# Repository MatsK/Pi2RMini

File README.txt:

Pi2RMini 
2013-2014 Logan Microelectronics

Small power switch for the Raspberry Pi. Free to use, modify, and distribute with proper attribution. This directory holds the current schematic and layout (Eagle v6.1.0), single layer PDF (not mirrored), code for ATTiny13 and Raspberry Pi, and older versions.

awjlogan@gmail.com
awjlogan.wordpress.com

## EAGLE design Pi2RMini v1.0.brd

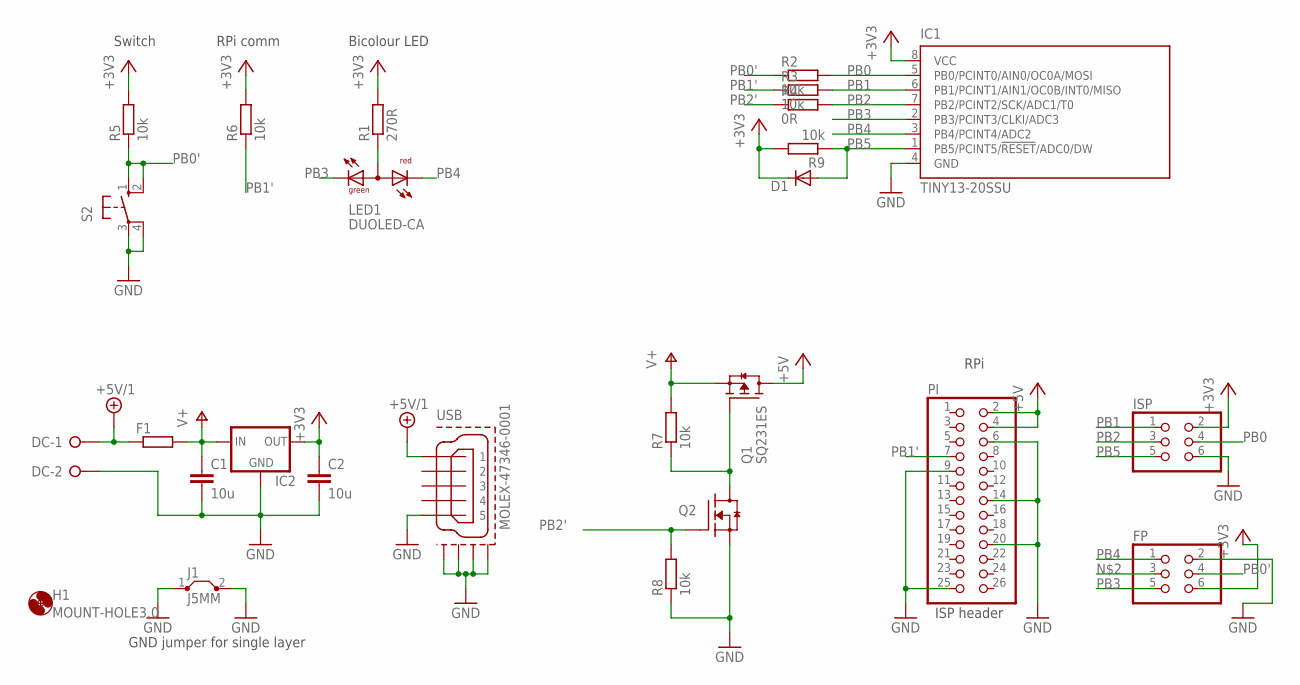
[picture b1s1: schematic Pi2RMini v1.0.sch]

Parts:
C1, C2: 10u; C0805
D1: DIODE-MICROMELF-R; MICROMELF-R
DC: W237-02P; W237-132
F1: R-EU_R1210; R1210
FP: PINHD-2X3; 2X03
H1: MOUNT-HOLE3.0; 3,0
IC1: TINY13-20SSU; 8S1
IC2: MCP1700TT; SOT-23
ISP: PINHD-2X3; 2X03
J1: J5MM; 05
LED1: DUOLED-CA; SOT-23
PI: PINHD-2X13; 2X13
Q1: SQ231ES; SOT-23
Q2: 2N7002; SOT-23
R1: 270R; R0805
R2, R3, R5, R6, R7, R8, R9: 10k; R0805
R4: 0R; R0805
S2: 10-XX; B3F-10XX
USB: MOLEX-47346-0001; MOLEX-47364-0001

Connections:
+3V3: C2.1, D1.C, FP.6, IC1.8 (VCC), IC2.2 (OUT), ISP.2, R1.2, R5.2, R6.2, R9.2
+5V: PI.2, PI.4, Q1.3 (D)
+5V/1: DC.1, F1.1, USB.1
GND: C1.2, C2.2, DC.2, FP.2, IC1.4 (GND), IC2.1 (GND), ISP.6, J1.1, J1.2, PI.6, PI.9, PI.14, PI.20, PI.25, Q2.2 (S), R8.1, S2.3, S2.4 (P1), USB.5, USB.GND1, USB.GND2, USB.GND3, USB.GND4
unnamed: FP.3, LED1.3 (A), R1.1
unnamed: Q1.1 (G), Q2.3 (D), R7.1
PB0: IC1.5 (PB0/PCINT0/AIN0/OC0A/MOSI), ISP.4, R2.2
PB0': FP.4, R2.1, R5.1, S2.1 (S), S2.2 (S1)
PB1: IC1.6 (PB1/PCINT1/AIN1/OC0B/INT0/MISO), ISP.1, R3.2
PB1': PI.7, R3.1, R6.1
PB2: IC1.7 (PB2/PCINT2/SCK/ADC1/T0), ISP.3, R4.2
PB2': Q2.1 (G), R4.1, R8.2
PB3: FP.5, IC1.2 (PB3/PCINT3/CLKI/ADC3), LED1.2 (CG)
PB4: FP.1, IC1.3 (PB4/PCINT4/ADC2), LED1.1 (CR)
PB5: D1.A, IC1.1 (PB5/PCINT5/!RESET!/ADC0/DW), ISP.5, R9.1
V+: C1.1, F1.2, IC2.3 (IN), Q1.2 (S), R7.2

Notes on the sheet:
Switch
RPi comm
Bicolour LED
GND jumper for single layer
ISP header
RPi

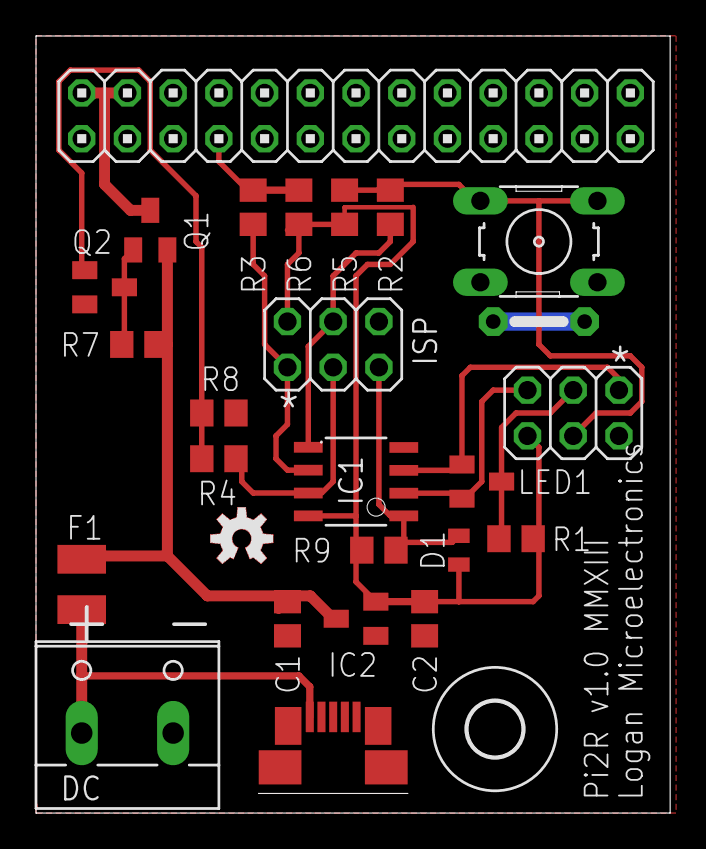
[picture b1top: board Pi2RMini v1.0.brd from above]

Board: 2 copper layers, 35.2 x 43.2 mm, 26 parts (0 on the bottom side), 16 nets.

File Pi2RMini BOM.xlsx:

Pi2RMini BOM file
Sch. # | Part | Package | Farnell Code | Price / 100 | Notes |  | Total ex. VAT | 2.2409999999999997
C1 | 10u ceramic | 0805 | 1288204 | 6.6000000000000003E-2 |  |  | VAT | 0.44819999999999993
C2 | 10u ceramic | 0805 | 1288204 | 6.6000000000000003E-2 |  |  | Total | 2.6891999999999996
IC1 | ATtiny13 | SOIC8 | 1715519 | 0.36
IC2 | MCP1700 | SOT23 | 1296952 | 0.19700000000000001 |  |  | Total parts
Q2 | 2N7002 | SOT23 | 2317616 | 0.02 |  |  | Total unique
Q1 | SQ2319ES | SOT23 | 1869886 | 0.32
USB | micro USB B | n/a | 1568026 | 0.48 | optional
LED1 | Bicolour LED | SOT23 | 2146479 | 0.17399999999999999 | optional
R1 | 270R | 0805 | 2331788 | 6.0000000000000001E-3
R2 | 10K | 0805 | 2331808 | 6.0000000000000001E-3
R3 | 10K | 0805 | 2331808 | 6.0000000000000001E-3
R4 | 0R | jumper
R5 | 10K | 0805 | 2331808 | 6.0000000000000001E-3
R6 | 10K | 0805 | 2331808 | 6.0000000000000001E-3
R7 | 10K | 0805 | 2331808 | 6.0000000000000001E-3
R8 | 10K | 0805 | 2331823 | 6.0000000000000001E-3
ISP | 2x3 header | n/a | 1248132 | 0.23
FP | 2x3 header | n/a | 1248132 | 0.23
SW | switch | n/a | 9471731 | 3.7999999999999999E-2
R9 | 10K | 0805 | 2331808 | 6.0000000000000001E-3
D1 | LL4148 | miniMELF | 7355513 | 1.2E-2 | optional

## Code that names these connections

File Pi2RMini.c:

/*
 * Pi2RMini.c
 *
 * Pi2R Mini device firmware for v1.0 boards
 * Logan Microelectronics 2013-2014
 * http://awjlogan.wordpress.com
 * https://github.com/awjlogan/pi2rmini
 *
 * Written in AVR Studio 5 for AVR GCC
 * Target: Atmel ATTiny13
 * 4.8 MHz internal osscilator / 8 = 600 kHz
 * Pins:	1	!RST					PB5
 *			2	Green LED				PB3
 *			3	Red LED					PB4
 *			4	GND		
 *			5	Switch					PB0
 *			6	RPi communication line	PB1
 *			7	RPi MOSET				PB2
 *			8	+3V3
 *
 * Fuse calculated:		69 FF (http://www.engbedded.com/fusecalc)
 * avrdude arguments:	-U lfuse:w:0x69:m -U hfuse:w:0xff:m
 * for: 4.8 MHz int osc, 14CK + 64 ms startup, CKDIV, no WDT, SPI enabled, !RST enabled, no BOD
 *
 * To change the startup, reset, and shutdown delays, alter lines with 'seconds = xx'. The TMR0 interrupt hits every
 * ~100 ms, so the seconds value should be 'delay in seconds x 10'. The variable 'flash' acts in the same way.
*/			

#define F_CPU		600000UL

#include <avr/io.h>
#include <avr/interrupt.h>
#include <util/delay.h>

// Status register definitions
#define	PI_ERROR	1
#define PI_ON		8
#define PI_OFF		16
#define BUTTON		32

#define PI_COMM		PINB1

// Pin assignments
#define SW			0x01
#define PI_FET		0x04
#define LED_G		0x08
#define LED_R		0x10

// common cathode status LED on/off
#define RED_OFF		PORTB &= ~(LED_R)
#define RED_ON		PORTB |= LED_R
#define GRN_OFF		PORTB &= ~(LED_G)
#define GRN_ON		PORTB |= LED_G

// Function prototypes
static void setup(void);
static void button(void);
static void reset(void);

// Global variables
static volatile uint8_t state = 0;
static volatile uint8_t flash = 0;
static volatile uint_least16_t seconds = 0;

int main(void)
{
	setup();
	state |= PI_OFF;
	RED_ON;
	GRN_OFF;
	
	// check status registers and respond
	while(1)
    {	
		if (state & BUTTON) {
			// disable PCINT while button press is handled
			PCMSK &= ~(1<<PCINT0);
			state &= ~(BUTTON);
			_delay_ms(50);					// debounce
			if (!(PINB & PINB0)) {
				button();
			}
			PCMSK |= (1<<PCINT0);
		}
		
		// flash red LED if in error state
		if (state & PI_ERROR) {
			if (!flash) {
				PORTB ^= LED_R;
				flash = 2;
			}
		}
	}	
}

static void button(void) {
	if (state & PI_OFF) {
		state = PI_ON;
		PORTB |= PI_FET;
		GRN_ON;
		RED_ON;
		
		// wait 60 secs for RPi to start up
		seconds = 600;
		while(PINB & (1<<PI_COMM)) {
			if (!seconds) {
				state |= PI_ERROR;
				GRN_OFF;
				return;
			}
		}
		RED_OFF;
		return;
	}
	
	if (state & PI_ON) {
		// check for forced reset - 4 s press
		seconds = 40;
		RED_ON;
		GRN_OFF;
		while (!(PINB & (1<<PINB0))) {
			// flash red/green
			if (!flash) {
				PORTB ^= (LED_G + LED_R);
				flash = 2;
			}
			// time up, reset!
			if (!seconds) {
				cli();
				reset();
				while(!(PINB & (1<<PINB0)));
				sei();
				return;
			}
		}
		
		// don't turn off in error state
		if (state & PI_ERROR) {
			RED_ON;
			GRN_OFF;
			return;
		}		
		
		// send shutdown signal, wait 10 secs for response
		RED_ON;
		GRN_OFF;
		DDRB |= (1<<DDB1);
		PORTB |= (1<<PINB1);
		_delay_ms(1);
		PORTB &= ~(1<<PINB1);
		_delay_ms(100);
		DDRB &= ~(1<<DDB1);
		PORTB |= (1<<PINB1);
		seconds = 100;
		while(PINB & (1<<PI_COMM)) {
			if (!seconds) {
				RED_ON;
				GRN_OFF;
				state |= PI_ERROR;
				return;
			}
		}
		
		// wait 30 secs, then shutdown
		GRN_ON;
		seconds = 300;
		while(seconds) {}
		reset();
		return;
	}
}

static void reset(void) {
	state = PI_OFF;
	PORTB = LED_R;
	DDRB = ((1<<DDB2)|(1<<DDB3)|(1<<DDB4));	
	return;
}

static void setup(void) {
	cli();
	
	// oscillator setup
	CLKPR = 0x80;	
	CLKPR = 0x03;
	
	// interrupt setup
	PCMSK |= 1 << PCINT0;	
	GIMSK |= 1 << PCIE;
	TIMSK0 |= 1 << TOIE0;
	
	// TMR0 setup
	// TCNT0 = 21 will give 0.1s count up time
	TCCR0A = 0;		
	TCCR0B = 0x05;	
					
	// PORTB setup
	MCUCR |= (1<<PUD);
	DDRB = ((1<<DDB2)|(1<<DDB3)|(1<<DDB4));	

	sei();
}

ISR(PCINT0_vect) {
	state |= BUTTON;
}

ISR(TIM0_OVF_vect) {
	if(flash) flash--;
	if(seconds) seconds--;
	TCNT0 = 21;					// reset for ~100 ms interval
}

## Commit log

2014-03-01 First version
2014-03-07 Added v1.0 schematic
2014-03-16 Software revision
